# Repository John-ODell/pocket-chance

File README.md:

Pocket Chance (J'Boy) - John O'Dell

A pocket casino for the Waveshare RP2040-Plus and the Waveshare 1.3" LCD HAT, written in MicroPython. It runs offline on the board. Three games: Blackjack, Ultimate Texas Hold'em and John's own Caribbean, a flop game with a low or high call.

The HAT plugs onto the board, so there is no wiring in this project. The pin map and everything we measured on a real board is in [`docs/HARDWARE.md`](docs/HARDWARE.md).

This project was built with a small team of AI sessions (a PM, a developer and a hardware expert) directing one person. How that works, with role files and starter prompts you can reuse, is in [`docs/AI_TEAM.md`](docs/AI_TEAM.md).

Last updated: 2026-10-04

## Items needed
- Waveshare RP2040-Plus (16 MB version)
- Waveshare Pico LCD 1.3" HAT (240 x 240 screen, joystick, 4 buttons)
- USB-C data cable
- A computer with Python 3.9 or newer

## Quick start
The full follow-along guide is [`SETUP.md`](SETUP.md). The short version:

1. Download the **16 MB** MicroPython firmware for the RP2040-Plus from micropython.org. Hold BOOTSEL, plug in, drag the `.uf2` onto the `RPI-RP2` drive.
2. `pip install mpremote pillow`
3. Copy the files to the board with `mpremote fs cp` (exact commands in `SETUP.md`, Step 4).
4. `mpremote run pocket.py`

You should see the menu: "Pocket Chance", your chips, and the games.

If the screen stays dark, open `pocket.py` and set `FAST_SPI = False`. That is the only board-specific setting (see `docs/HARDWARE.md`, "The one trap").

## Controls
Landscape, with USB-C and the joystick on the left and the buttons on the right.

| Where | Control | Does |
|---|---|---|
| Menu | Joystick up / down | Move the box (the list scrolls) |
| Menu | **A** | Pick a game. "Off" stops the program |
| Blackjack, betting | Joystick up / down | Change the bet (5 to 500, steps of 5) |
| Blackjack, betting | **A** deal, **B** back to menu | |
| Blackjack, playing | **A** hit, **B** stand, **X** double, **Y** split a pair | |
| Ultimate, betting | Joystick, **A** deal, **X** help, **B** menu | Blind equals the Ante |
| Ultimate, pre-flop / flop / river | **A** raise (4x / 2x / 1x), **Y** raise 3x pre-flop, **B** check (fold at the river) | The table cards turn as you go; the river prompt shows the dealer outs |
| Caribbean, betting | Joystick up / down, left / right | Change the Ante (5 to 50, capped at a fifth of your chips) |
| Caribbean, betting | **A** deal, **X** help, **B** menu | |
| Caribbean, flop | **A** call high (4x the Ante), **Y** call low (2x), **B** fold | The last two table cards turn, then the dealer's cards one by one |

## Games

| Game | Status | Rules | House edge |
|---|---|---|---|
| Blackjack | **Playable** | 6 decks, reshuffle at 75% dealt, dealer stands on all 17, blackjack pays 3:2, hit / stand / double, split pairs once (aces get one card each, double after split allowed) | about 0.55% |
| Ultimate Texas Hold'em ("Ultimate") | **Playable** | Equal Ante and Blind (5 to 50), two hole cards, five table cards; raise 4x or 3x pre-flop, 2x after the flop, 1x at the river or fold; dealer needs a pair for the Ante to count; Blind pays straight 1:1 up to royal 500:1. X teaches the full published simple strategy and the river prompt shows the dealer-outs count (`UTH_HINT`). Four other players sit at the sides as chip stacks (`UTH_SEATS`) | about 2.4% of the ante with the taught strategy, 2.2% optimal |
| Caribbean (John's flop game) | **Playable** | Ante 5 to 50, two cards each, the first three table cards turn, then call high (4x) or low (2x) or fold, the last two turn; best five of seven; the dealer needs a pair of fours or better, otherwise every bet pushes; a winning Ante pays by a table (flush 2:1, full house 3:1, quads 10:1, straight flush 20:1, royal 100:1, else 1:1), the call 1:1. When you and all four seats beat a dealer hand, a win on the next hand pays three times (Ante and call together). Four chip-stack seats (`CAR_SEATS`). The published game this is based on is Casino Hold'em (one call size, 2.16% optimal) | about 5% of the ante with the taught strategy (15% without the multiplier) |
| Caribbean Stud | Archived (John's ruling, 2026-10-06) | Was on the board as "Caribbean" until step 1n; code in `archive/stud/` | 5.2% |
| Slots | Shelved | A 3-reel machine was built and tuned (93.84% return) then dropped: a classic multi-line machine does not fit the board's RAM. Code kept in `archive/slots/` | n/a |

Chips: you start with 1000. If you go broke you get a free refill. Your chips are saved to the board after every round, with a backup copy and recovery if the save is damaged.

The house edges were measured by simulation (`tools/bj_edge.py`, `tools/bj_split.py`, `tools/uth_edge.py`, `tools/casino_holdem_edge.py`; `archive/stud/stud_edge.py` for the archived game) and the rules were checked against the public references on wizardofodds.com.

## What it does well on this hardware
- Full-speed screen: about 58 frames a second for a full redraw, once the board's peripheral clock is set from the system PLL (one `machine.freq` call at the top of `pocket.py`, see `docs/HARDWARE.md`).
- Redraws only the strip of the screen that changed, so a button press answers in about 15 to 100 ms.
- About 50 to 55 KB of RAM left while playing, on a board with 264 KB.
- Art is optional. With no image files the game draws cards and the table in code.

## Your own art (optional)
Sizes, names, and where text sits on each screen are in [`assets/ASSETS.md`](assets/ASSETS.md). In short: draw one 24-bit BMP per picture, magenta (255, 0, 255) is transparent, run `python3 tools/convert_assets.py`, and copy the files it writes to `/assets/` on the board. The menu background is a full-screen 240 x 240 image you supply yourself (`assets/src/ui/menu_background.bmp`). None is included.

## Repository layout
```
pocket.py          the game's start file on the board (menu)
lib/               shared modules for the board: screen, fonts, buttons, images, saving, cards, clock fix, poker
games/             one set of modules per game: rules, table logic, screens
archive/           shelved work (slots)
assets/            art spec and the converter's input and output folders
tools/             Mac-side tools: image converter, odds simulators, upload checker
tests/             automated tests (run on a computer, no board needed)
hw/ hwtest/        measured hardware budget, board notes, reviews, and the benchmark scripts
docs/              hardware reference sheet, the AI team guide, role files
pcb/               workspace for designing your own board from this hardware (first-timer guide, in progress)
pm/                decision requests, rulings, decision log, hand-off notes
SETUP.md           follow-along install guide
UPLOAD.md          exact file list for the board, checked by tools/check_upload.py
main_monolith.py   the original single-file program this project replaced (read-only)
```

## Running the tests
```bash
python3 -m unittest discover -s tests
```
They run on a normal computer with stand-in modules for the board.

## Troubleshooting
| What you see | What to do |
|---|---|
| The board does not show up | Use a data cable. Close Viper IDE and its tab: only one program can use the USB port at a time |
| Dark screen | `FAST_SPI = False` in `pocket.py` |
| "no module named ..." | A file is missing or in the wrong folder. Compare with `SETUP.md`, Step 4 |
| "could not enter raw repl" | The board is fine. Unplug it, or run `hwtest/unwedge.py` |

More in [`SETUP.md`](SETUP.md).

## Credits
- The screen driver and font in `main_monolith.py`, and the code adapted from it, started from Tony Goodhew's Waveshare 1.3" workout (August 2021).
- Rules and house edges were checked against the public pages on wizardofodds.com.
- MicroPython firmware is a public download from micropython.org and is not stored here.
- Waveshare datasheets and demo code are not included.

## Issues
Open an issue with the step you were on, what you saw, and the full terminal output. Please do not post anything private.

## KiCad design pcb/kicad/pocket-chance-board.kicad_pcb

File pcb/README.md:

# pcb/: designing your own board

This folder is the workspace for turning the Pocket Chance hardware (a Waveshare RP2040-Plus plus a 1.3" LCD HAT) into **your own dev board**, ordered from a PCB fab such as PCBWay or JLCPCB. It is for someone doing this the first time.

**Status:** workspace set up. **Stage 1 (understand, no design choices)** comes first: the PCB maker writes `CONSTRAINTS.md` and `HOW_A_BOARD_IS_MADE.md`. Stage 2, what the first design adds, starts when the owner says so. See [`PLAN.md`](PLAN.md).

| File | What it is |
|---|---|
| [`PLAN.md`](PLAN.md) | The roadmap, the decisions to make first, rough costs, risks, and tools |
| [`INTAKE.md`](INTAKE.md) | What to read before designing: the project's measured hardware notes and the manufacturer documents |
| [`requirements/REQUIREMENTS.md`](requirements/REQUIREMENTS.md) | What the new board must do, with the source of every fact |
| [`../docs/roles/PCB_MAKER.md`](../docs/roles/PCB_MAKER.md) | The role file and starter prompt for the Claude session that guides you |
| `kicad/`, `bom/`, `fab/`, `reviews/` | KiCad project, bill of materials, files for the fab, and design reviews (empty for now) |
| `refs/` | Local copies of datasheets. **Not committed** (git ignores it) |

## How to start
1. Open a new Claude Code session in the repo folder and paste the starter prompt from `docs/roles/PCB_MAKER.md`.
2. Install KiCad (free): `brew install --cask kicad`, or download it from kicad.org.
3. Put the manufacturer PDFs you own into `pcb/refs/`.
4. Answer the questions one at a time. The PCB maker teaches each step.

## Request and review numbering (PM ruling, 2026-10-04)
PCB decision requests use their own prefix so they never clash with the developer's: `pm/inbox/PCB-001-slug.md`, rulings `pm/outbox/PCB-001.md`, and the expert's reviews of them `hw/reviews/HR-P01.md`. The one exception is the first scope request, which keeps its original number: `pm/inbox/DR-033-board-scope.md` (reviewed in `hw/reviews/HR-033.md`).

The PCB maker prepares everything for ordering and gives you a checklist. **You** place the order and enter payment details. It never does.

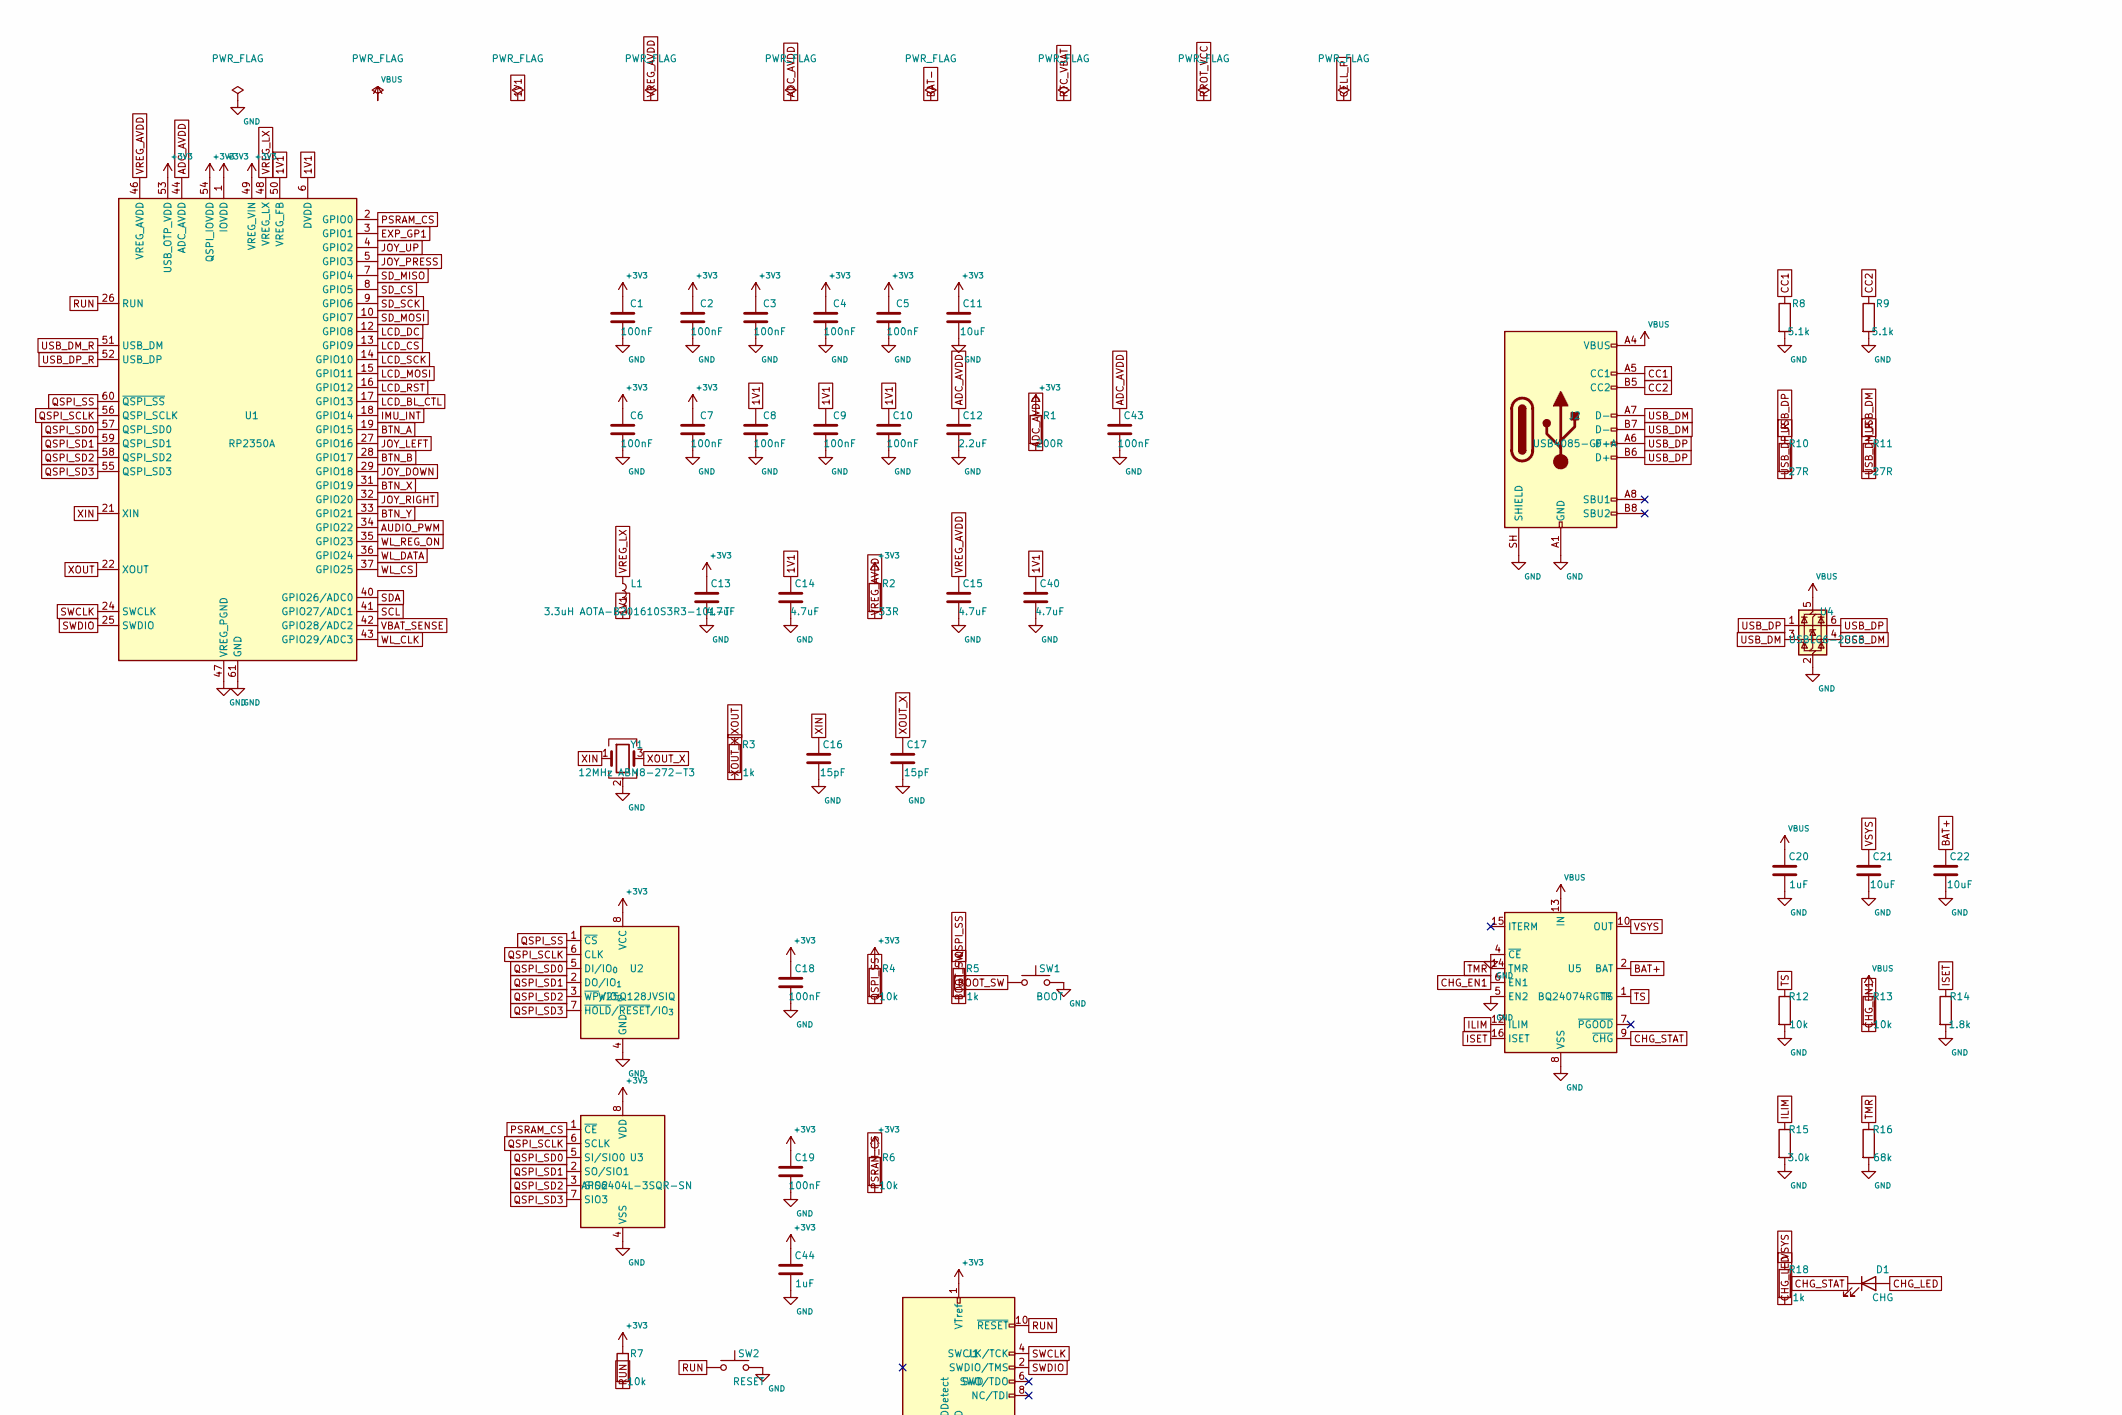
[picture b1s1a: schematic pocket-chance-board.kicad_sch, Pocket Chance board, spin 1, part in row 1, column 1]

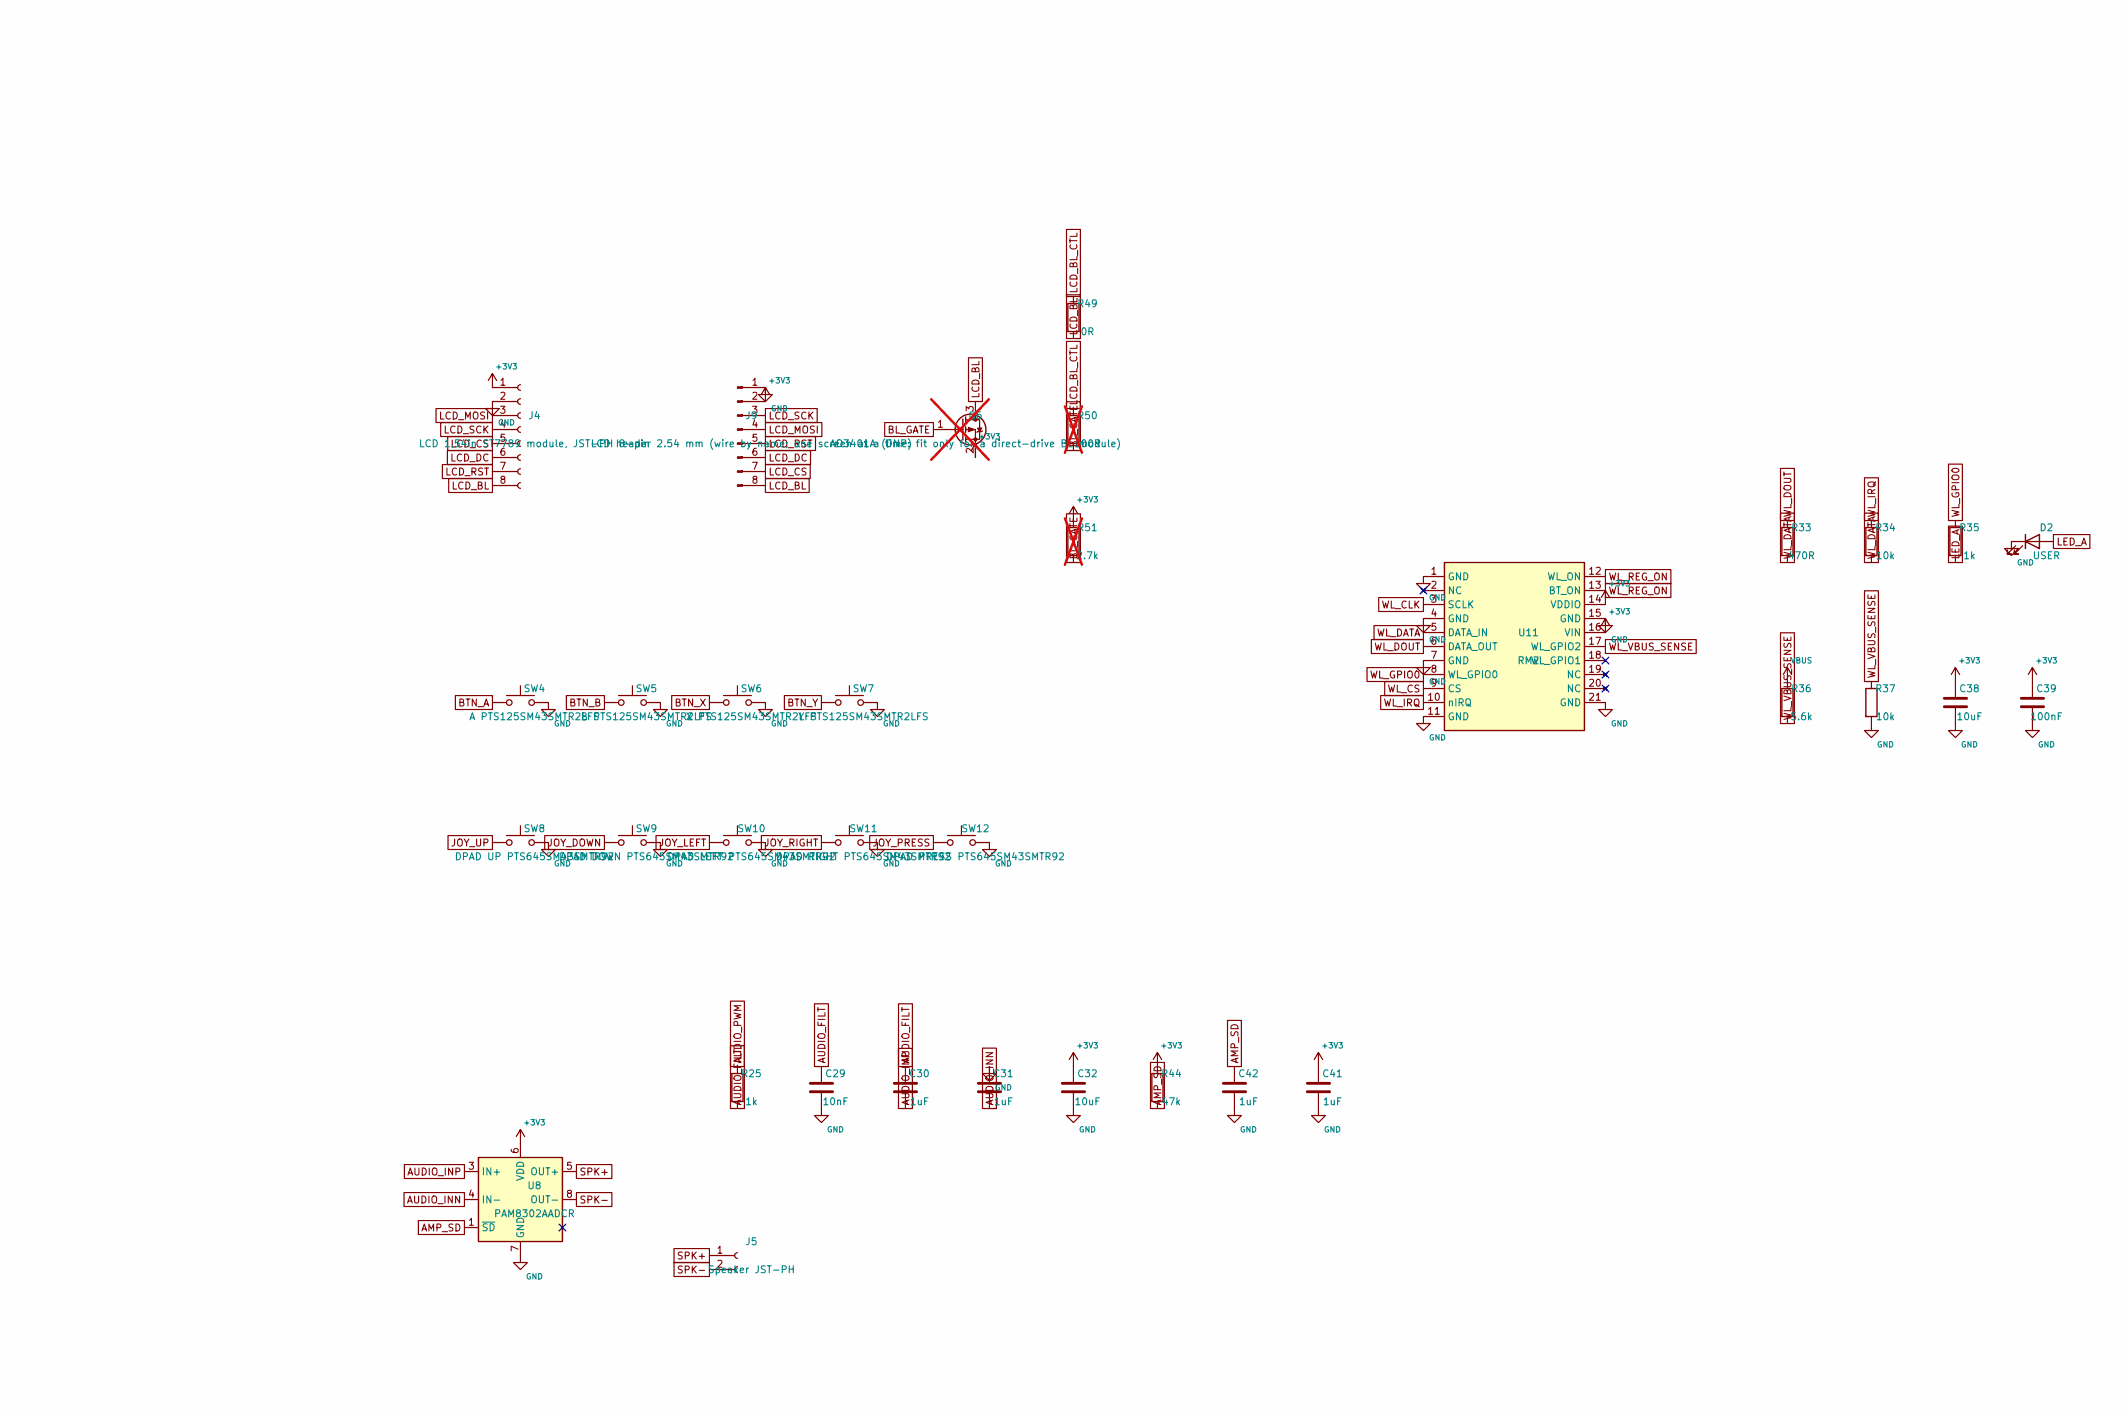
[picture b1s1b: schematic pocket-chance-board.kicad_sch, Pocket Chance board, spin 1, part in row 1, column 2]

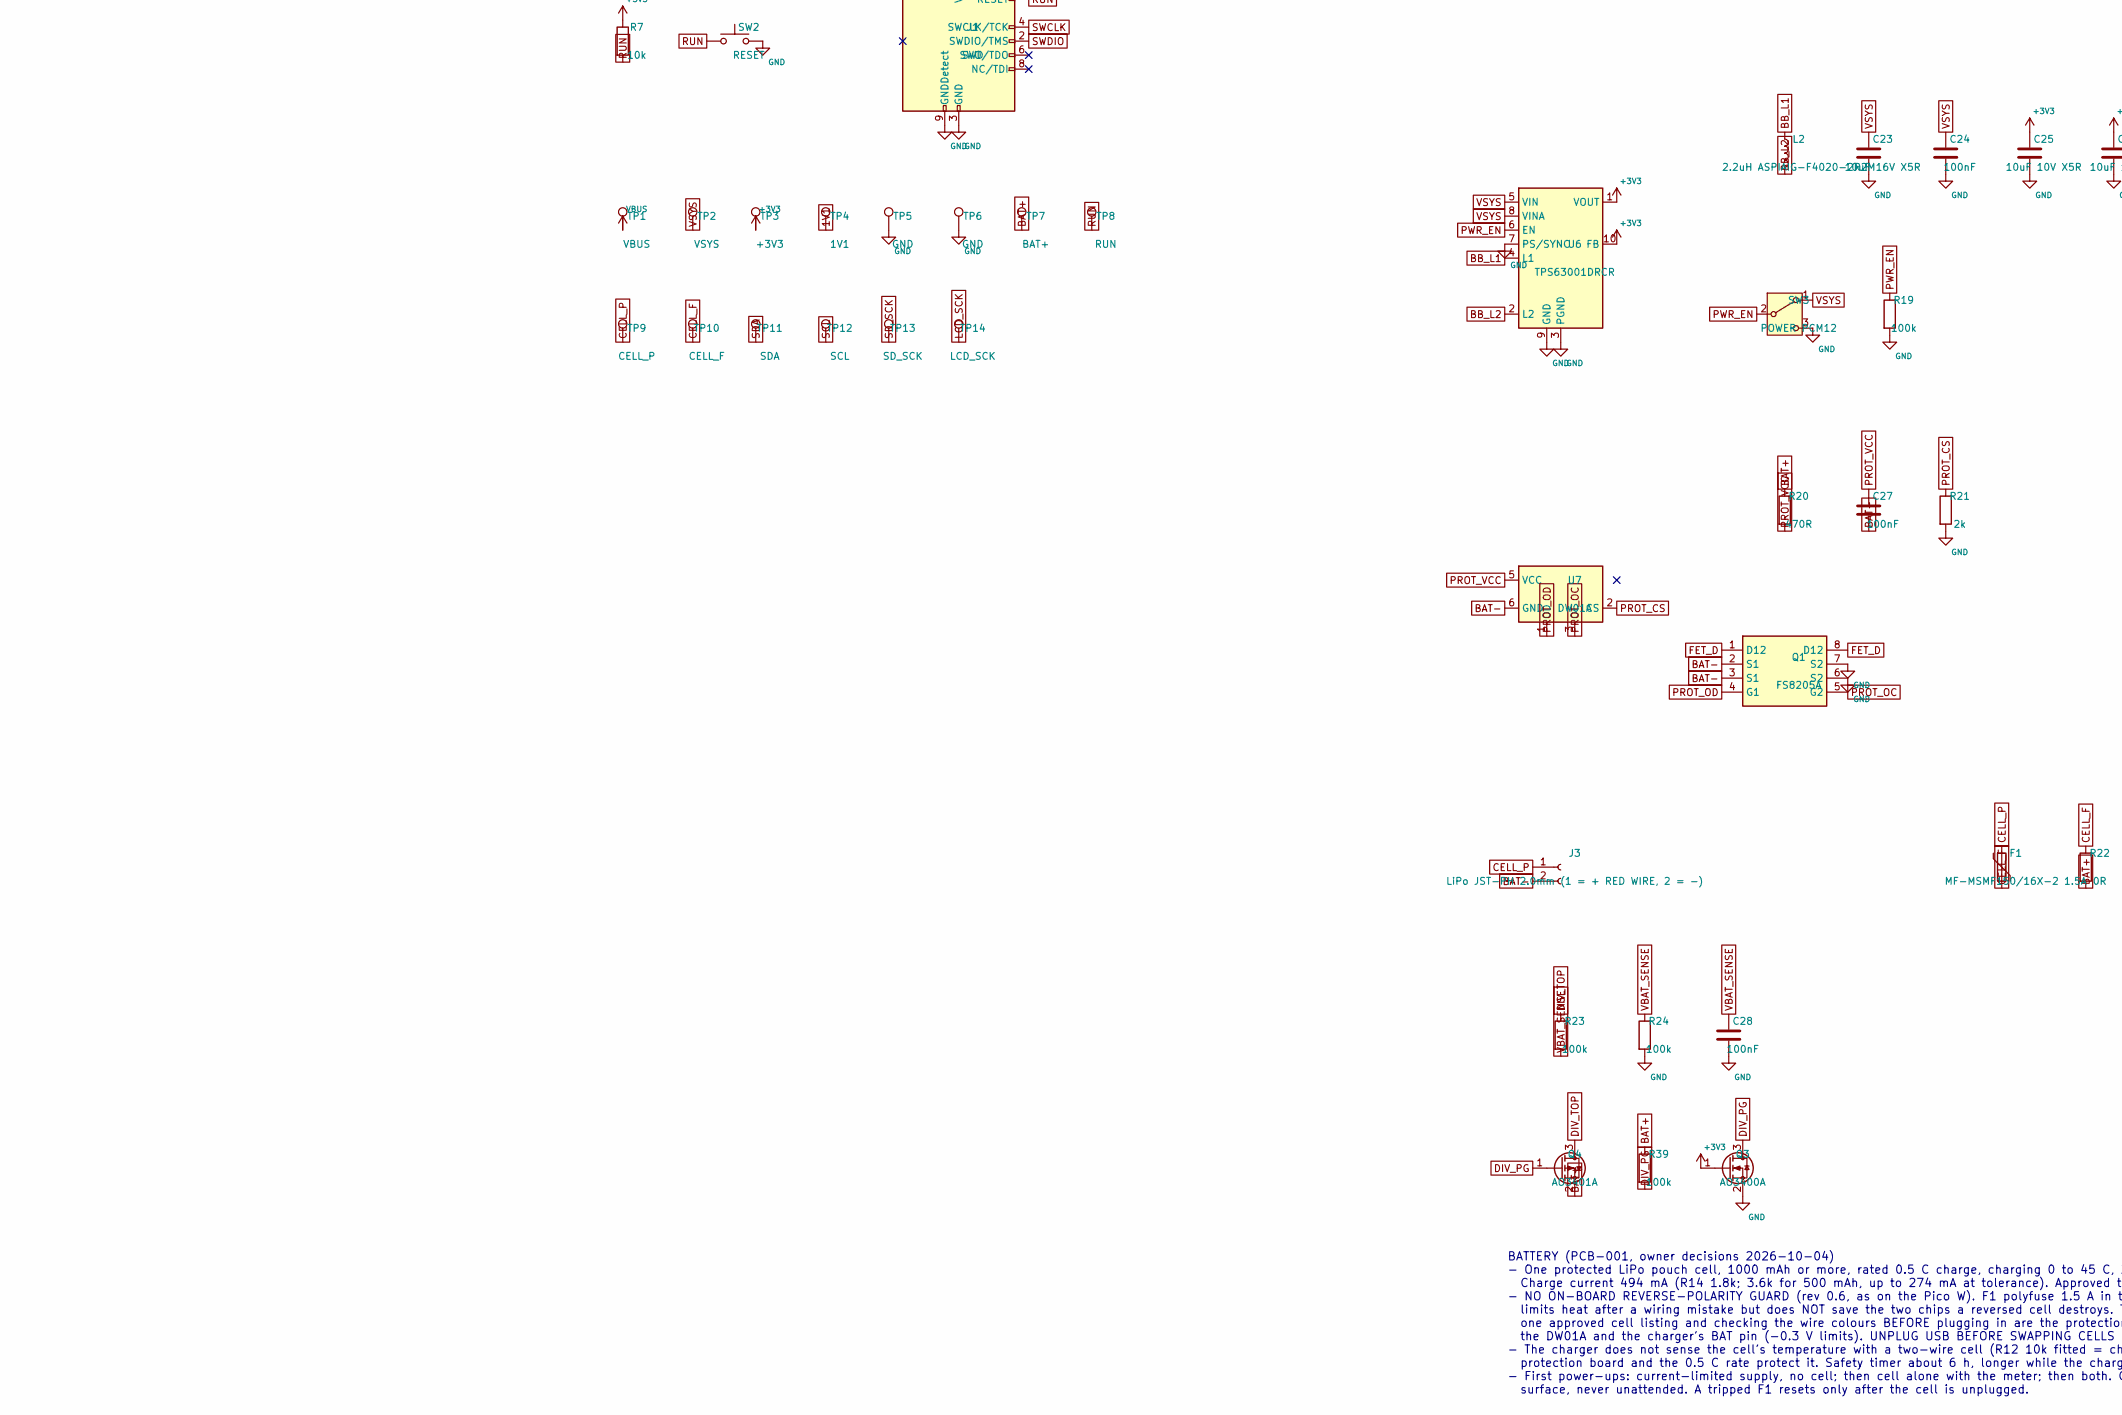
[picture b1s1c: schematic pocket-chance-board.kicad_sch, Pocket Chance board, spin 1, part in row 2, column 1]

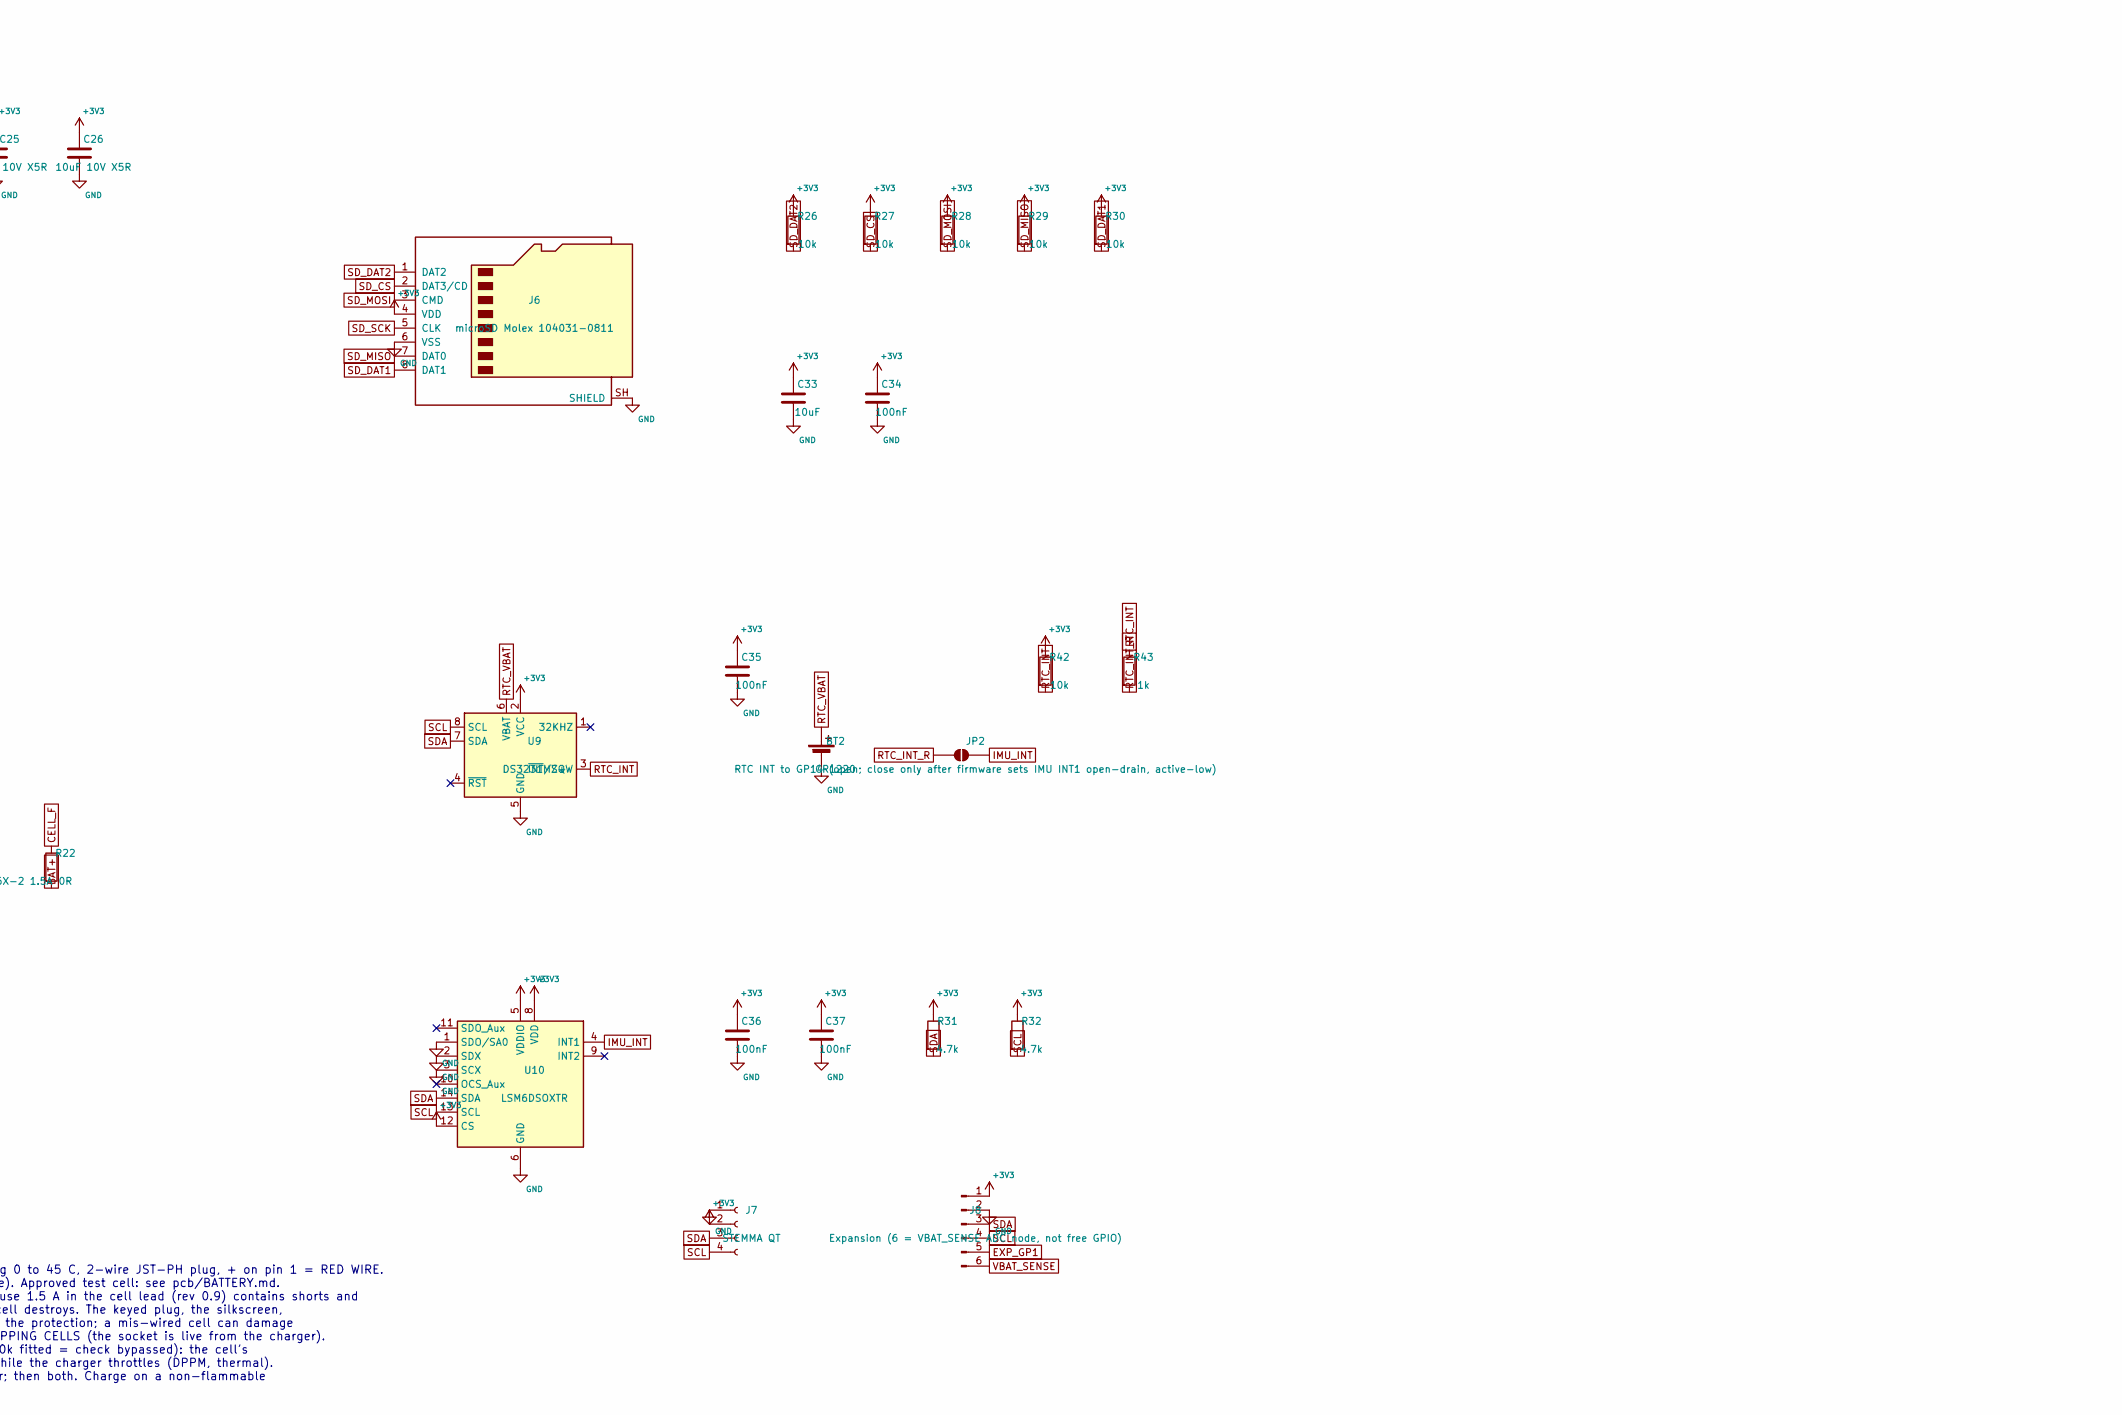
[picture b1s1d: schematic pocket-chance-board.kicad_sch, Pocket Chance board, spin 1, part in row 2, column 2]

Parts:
BT2: CR1220; BatteryHolder_Keystone_3001_1x12mm
C1, C2, C3, C4, C5, C6, C7, C8, C9, C10, C18, C19, C24, C27, C28, C34, C35, C36, C37, C39, C43: 100nF; C_0402_1005Metric
C11, C21, C22, C32, C33, C38: 10uF; C_0603_1608Metric
C12: 2.2uF; C_0603_1608Metric
C13, C14, C15, C40: 4.7uF; C_0402_1005Metric
C16, C17: 15pF; C_0402_1005Metric
C20, C30, C31, C41, C42, C44: 1uF; C_0603_1608Metric
C23: 10uF 16V X5R; C_0805_2012Metric
C25, C26: 10uF 10V X5R; C_0805_2012Metric
C29: 10nF; C_0402_1005Metric
D1: CHG; LED_0603_1608Metric
D2: USER; LED_0603_1608Metric
F1: MF-MSMF150/16X-2 1.5A; Fuse_Bourns_MF-MSMF_1812
J1: SWD; PinHeader_2x05_P1.27mm_Vertical_SMD
J2: USB4085-GF-A; USB_C_Receptacle_GCT_USB4085
J3: LiPo JST-PH 2.0mm (1 = + RED WIRE, 2 = -); JST_PH_S2B-PH-SM4-TB_1x02-1MP_P2.00mm_Horizontal
J4: LCD 1.54in ST7789 module, JST-PH 8-pin; JST_PH_S8B-PH-SM4-TB_1x08-1MP_P2.00mm_Horizontal
J5: Speaker JST-PH; JST_PH_S2B-PH-SM4-TB_1x02-1MP_P2.00mm_Horizontal
J6: microSD Molex 104031-0811; microSD_HC_Molex_104031-0811
J7: STEMMA QT; JST_SH_SM04B-SRSS-TB_1x04-1MP_P1.00mm_Horizontal
J8: Expansion (6 = VBAT_SENSE ADC node, not free GPIO); PinHeader_1x06_P2.54mm_Vertical
J9: LCD header 2.54 mm (wire by name; one screen at a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; PinHeader_1x08_P2.54mm_Vertical
JP2: RTC INT to GP14 (open; close only after firmware 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; SolderJumper-2_P1.3mm_Open_Pad1.0x1.5mm
L1: 3.3uH AOTA-B201610S3R3-101-T; AOTA-B201610S
L2: 2.2uH ASPIAIG-F4020-2R2M; L_Abracon_ASPIAIG-F4020
Q1: FS8205A; TSSOP-8_4.4x3mm_P0.65mm
Q3: AO3400A; SOT-23
Q4: AO3401A; SOT-23
Q6: AO3401A (DNP: fit only for a direct-drive BL modu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; SOT-23; not fitted
R1: 200R; R_0402_1005Metric
R2: 33R; R_0402_1005Metric
R3, R5, R18, R25, R35, R43: 1k; R_0402_1005Metric
R4, R6, R7, R12, R13, R26, R27, R28, R29, R30, R34, R37, R42: 10k; R_0402_1005Metric
R8, R9: 5.1k; R_0402_1005Metric
R10, R11: 27R; R_0402_1005Metric
R14: 1.8k; R_0402_1005Metric
R15: 3.0k; R_0402_1005Metric
R16: 68k; R_0402_1005Metric
R19, R23, R24, R39: 100k; R_0402_1005Metric
R20, R33: 470R; R_0402_1005Metric
R21: 2k; R_0402_1005Metric
R22: 0R; R_0603_1608Metric
R31, R32: 4.7k; R_0402_1005Metric
R36: 5.6k; R_0402_1005Metric
R44: 47k; R_0402_1005Metric
R49: 0R; R_0402_1005Metric
R50: 100R; R_0402_1005Metric; not fitted
R51: 2.7k; R_0402_1005Metric; not fitted
SW1: BOOT; SW_SPST_PTS645Sx43SMTR92
SW2: RESET; SW_SPST_PTS645Sx43SMTR92
SW3: POWER PCM12; SW_SPDT_PCM12
SW4: A PTS125SM43SMTR2LFS; SW_Push_1P1T_NO_CK_PTS125Sx43SMTR
SW5: B PTS125SM43SMTR2LFS; SW_Push_1P1T_NO_CK_PTS125Sx43SMTR
SW6: X PTS125SM43SMTR2LFS; SW_Push_1P1T_NO_CK_PTS125Sx43SMTR
SW7: Y PTS125SM43SMTR2LFS; SW_Push_1P1T_NO_CK_PTS125Sx43SMTR
SW8: DPAD UP PTS645SM43SMTR92; SW_SPST_PTS645Sx43SMTR92
SW9: DPAD DOWN PTS645SM43SMTR92; SW_SPST_PTS645Sx43SMTR92
SW10: DPAD LEFT PTS645SM43SMTR92; SW_SPST_PTS645Sx43SMTR92
SW11: DPAD RIGHT PTS645SM43SMTR92; SW_SPST_PTS645Sx43SMTR92
SW12: DPAD PRESS PTS645SM43SMTR92; SW_SPST_PTS645Sx43SMTR92
TP1: VBUS; TestPoint_Pad_D1.5mm
TP2: VSYS; TestPoint_Pad_D1.5mm
TP3: +3V3; TestPoint_Pad_D1.5mm
TP4: 1V1; TestPoint_Pad_D1.5mm
TP5, TP6: GND; TestPoint_Pad_D1.5mm
TP7: BAT+; TestPoint_Pad_D1.5mm
TP8: RUN; TestPoint_Pad_D1.5mm
TP9: CELL_P; TestPoint_Pad_D1.5mm
TP10: CELL_F; TestPoint_Pad_D1.5mm
TP11: SDA; TestPoint_Pad_D1.5mm
TP12: SCL; TestPoint_Pad_D1.5mm
TP13: SD_SCK; TestPoint_Pad_D1.5mm
TP14: LCD_SCK; TestPoint_Pad_D1.5mm
U1: RP2350A; QFN-60-1EP_7x7mm_P0.4mm_EP3.4x3.4mm
U2: W25Q128JVSIQ; SOIC-8_5.3x5.3mm_P1.27mm
U3: APS6404L-3SQR-SN; SOIC-8_3.9x4.9mm_P1.27mm
U4: USBLC6-2SC6; SOT-23-6
U5: BQ24074RGTR; VQFN-16-1EP_3x3mm_P0.5mm_EP1.68x1.68mm_ThermalVias
U6: TPS63001DRCR; Texas_DRC0010J_ThermalVias
U7: DW01A; SOT-23-6
U8: PAM8302AADCR; SOIC-8_3.9x4.9mm_P1.27mm
U9: DS3231MZ+; SOIC-8_3.9x4.9mm_P1.27mm
U10: LSM6DSOXTR; LGA-14_3x2.5mm_P0.5mm_LayoutBorder3x4y
U11: RM2
Y1: 12MHz ABM8-272-T3; Crystal_SMD_3225-4Pin_3.2x2.5mm

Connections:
1V1: C8.1, C9.1, C10.1, C14.1, C40.1, L1.2, TP4.1, U1.6 (DVDD), U1.23 (DVDD), U1.39 (DVDD), U1.50 (VREG_FB)
+3V3: C1.1, C2.1, C3.1, C4.1, C5.1, C6.1, C7.1, C11.1, C13.1, C18.1, C19.1, C25.1, C26.1, C32.1, C33.1, C34.1, C35.1, C36.1, C37.1, C38.1, C39.1, C41.1, C44.1, J1.1 (VTref), J4.1, J6.4 (VDD), J7.2, J8.1, J9.2, Q3.1 (G), Q6.2 (S), R1.1, R2.1, R4.1, R6.1, R7.1, R26.1, R27.1, R28.1, R29.1, R30.1, R31.1, R32.1, R42.1, R44.1, R51.1, TP3.1, U1.1 (IOVDD), U1.11 (IOVDD), U1.20 (IOVDD), U1.30 (IOVDD), U1.38 (IOVDD), U1.45 (IOVDD), U1.49 (VREG_VIN), U1.53 (USB_OTP_VDD), U1.54 (QSPI_IOVDD), U2.8 (VCC), U3.8 (VDD), U6.1 (VOUT), U6.10 (FB), U8.6 (VDD), U9.2 (VCC), U10.5 (VDDIO), U10.8 (VDD), U10.12 (CS), U11.14 (VDDIO), U11.16 (VIN)
ADC_AVDD: C12.1, C43.1, R1.2, U1.44 (ADC_AVDD)
AMP_SD: C42.1, R44.2, U8.1 (~SD)
AUDIO_FILT: C29.1, C30.1, R25.2
AUDIO_INN: C31.2, U8.4 (IN-)
AUDIO_INP: C30.2, U8.3 (IN+)
AUDIO_PWM: R25.1, U1.34 (GPIO22)
BAT+: C22.1, Q4.2 (S), R20.1, R22.2, R39.1, TP7.1, U5.2 (BAT), U5.3 (BAT)
BAT-: C27.2, J3.2, Q1.2 (S1), Q1.3 (S1), U7.6 (GND)
BB_L1: L2.1, U6.4 (L1)
BB_L2: L2.2, U6.2 (L2)
BL_GATE: Q6.1 (G), R50.2, R51.2
BOOT_SW: R5.2, SW1.1
BTN_A: SW4.1, U1.19 (GPIO15)
BTN_B: SW5.1, U1.28 (GPIO17)
BTN_X: SW6.1, U1.31 (GPIO19)
BTN_Y: SW7.1, U1.33 (GPIO21)
CC1: J2.A5 (CC1), R8.1
CC2: J2.B5 (CC2), R9.1
CELL_F: F1.2, R22.1, TP10.1
CELL_P: F1.1, J3.1, TP9.1
CHG_EN1: R13.2, U5.6 (EN1)
CHG_LED: D1.2 (A), R18.2
CHG_STAT: D1.1 (K), U5.9 (~CHG)
DIV_PG: Q3.3 (D), Q4.1 (G), R39.2
DIV_TOP: Q4.3 (D), R23.1
EXP_GP1: J8.5, U1.3 (GPIO1)
FET_D: Q1.1 (D12), Q1.8 (D12)
GND: BT2.2 (-), C1.2, C2.2, C3.2, C4.2, C5.2, C6.2, C7.2, C8.2, C9.2, C10.2, C11.2, C12.2, C13.2, C14.2, C15.2, C16.2, C17.2, C18.2, C19.2, C20.2, C21.2, C22.2, C23.2, C24.2, C25.2, C26.2, C28.2, C29.2, C31.1, C32.2, C33.2, C34.2, C35.2, C36.2, C37.2, C38.2, C39.2, C40.2, C41.2, C42.2, C43.2, C44.2, D2.1 (K), J1.3 (GND), J1.5 (GND), J1.9 (GNDDetect), J2.A1 (GND), J2.A12 (GND), J2.B1 (GND), J2.B12 (GND), J2.SH (SHIELD), J4.2, J6.6 (VSS), J6.SH (SHIELD), J7.1, J8.2, J9.1, Q1.6 (S2), Q1.7 (S2), Q3.2 (S), R8.2, R9.2, R12.2, R14.2, R15.2, R16.2, R19.2, R21.2, R24.2, R37.2, SW1.2, SW2.2, SW3.3 (C), SW4.2, SW5.2, SW6.2, SW7.2, SW8.2, SW9.2, SW10.2, SW11.2, SW12.2, TP5.1, TP6.1, U1.47 (VREG_PGND), U1.61 (GND), U2.4 (GND), U3.4 (VSS), U4.2 (GND), U5.4 (~CE), U5.5 (EN2), U5.8 (VSS), U5.17 (VSS), U6.3 (PGND), U6.7 (PS/SYNC), U6.9 (GND), U6.11 (PGND), U8.7 (GND), U9.5 (GND), U10.1 (SDO/SA0), U10.2 (SDX), U10.3 (SCX), U10.6 (GND), U10.7 (GND), U11.1 (GND), U11.4 (GND), U11.7 (GND), U11.11 (GND), U11.15 (GND), U11.21 (GND), Y1.2 (G), Y1.4 (G)
ILIM: R15.1, U5.12 (ILIM)
IMU_INT: JP2.2 (B), U1.18 (GPIO14), U10.4 (INT1)
ISET: R14.1, U5.16 (ISET)
JOY_DOWN: SW9.1, U1.29 (GPIO18)
JOY_LEFT: SW10.1, U1.27 (GPIO16)
JOY_PRESS: SW12.1, U1.5 (GPIO3)
JOY_RIGHT: SW11.1, U1.32 (GPIO20)
JOY_UP: SW8.1, U1.4 (GPIO2)
LCD_BL: J4.8, J9.8, Q6.3 (D), R49.2
LCD_BL_CTL: R49.1, R50.1, U1.17 (GPIO13)
LCD_CS: J4.5, J9.7, U1.13 (GPIO9)
LCD_DC: J4.6, J9.6, U1.12 (GPIO8)
LCD_MOSI: J4.3, J9.4, U1.15 (GPIO11)
LCD_RST: J4.7, J9.5, U1.16 (GPIO12)
LCD_SCK: J4.4, J9.3, TP14.1, U1.14 (GPIO10)
LED_A: D2.2 (A), R35.2
PROT_CS: R21.1, U7.2 (CS)
PROT_OC: Q1.5 (G2), U7.3 (OC)
PROT_OD: Q1.4 (G1), U7.1 (OD)
PROT_VCC: C27.1, R20.2, U7.5 (VCC)
PSRAM_CS: R6.2, U1.2 (GPIO0), U3.1 (~CE)
PWR_EN: R19.1, SW3.2 (B), U6.6 (EN)
QSPI_SCLK: U1.56 (QSPI_SCLK), U2.6 (CLK), U3.6 (SCLK)
QSPI_SD0: U1.57 (QSPI_SD0), U2.5 (DI/IO_{0}), U3.5 (SI/SIO0)
QSPI_SD1: U1.59 (QSPI_SD1), U2.2 (DO/IO_{1}), U3.2 (SO/SIO1)
QSPI_SD2: U1.58 (QSPI_SD2), U2.3 (~WP/IO_{2}), U3.3 (SIO2)
QSPI_SD3: U1.55 (QSPI_SD3), U2.7 (~HOLD/~RESET/IO_{3}), U3.7 (SIO3)
QSPI_SS: R4.2, R5.1, U1.60 (~QSPI_SS), U2.1 (~CS)
RTC_INT: R42.2, R43.1, U9.3 (~INT/SQW)
RTC_INT_R: JP2.1 (A), R43.2
RTC_VBAT: BT2.1 (+), U9.6 (VBAT)
RUN: J1.10 (~RESET), R7.2, SW2.1, TP8.1, U1.26 (RUN)
SCL: J7.4, J8.4, R32.2, TP12.1, U1.41 (GPIO27/ADC1), U9.8 (SCL), U10.13 (SCL)
SDA: J7.3, J8.3, R31.2, TP11.1, U1.40 (GPIO26/ADC0), U9.7 (SDA), U10.14 (SDA)
SD_CS: J6.2 (DAT3/CD), R27.2, U1.8 (GPIO5)
SD_DAT1: J6.8 (DAT1), R30.2
SD_DAT2: J6.1 (DAT2), R26.2
SD_MISO: J6.7 (DAT0), R29.2, U1.7 (GPIO4)
SD_MOSI: J6.3 (CMD), R28.2, U1.10 (GPIO7)
SD_SCK: J6.5 (CLK), TP13.1, U1.9 (GPIO6)
SPK+: J5.1, U8.5 (OUT+)
SPK-: J5.2, U8.8 (OUT-)
SWCLK: J1.4 (SWCLK/TCK), U1.24 (SWCLK)
SWDIO: J1.2 (SWDIO/TMS), U1.25 (SWDIO)
TMR: R16.1, U5.14 (TMR)
TS: R12.1, U5.1 (TS)
USB_DM: J2.A7 (D-), J2.B7 (D-), R11.1, U4.3 (I/O2), U4.4 (I/O2)
USB_DM_R: R11.2, U1.51 (USB_DM)
USB_DP: J2.A6 (D+), J2.B6 (D+), R10.1, U4.1 (I/O1), U4.6 (I/O1)
USB_DP_R: R10.2, U1.52 (USB_DP)
VBAT_SENSE: C28.1, J8.6, R23.2, R24.1, U1.42 (GPIO28/ADC2)
VBUS: C20.1, J2.A4 (VBUS), J2.A9 (VBUS), J2.B4 (VBUS), J2.B9 (VBUS), R13.1, R36.1, TP1.1, U4.5 (VBUS), U5.13 (IN)
VREG_AVDD: C15.1, R2.2, U1.46 (VREG_AVDD)
VREG_LX: L1.1, U1.48 (VREG_LX)
VSYS: C21.1, C23.1, C24.1, R18.1, SW3.1 (A), TP2.1, U5.10 (OUT), U5.11 (OUT), U6.5 (VIN), U6.8 (VINA)
WL_CLK: U1.43 (GPIO29/ADC3), U11.3 (SCLK)
WL_CS: U1.37 (GPIO25), U11.9 (CS)
WL_DATA: R33.2, R34.2, U1.36 (GPIO24), U11.5 (DATA_IN)
WL_DOUT: R33.1, U11.6 (DATA_OUT)
WL_GPIO0: R35.1, U11.8 (WL_GPIO0)
WL_IRQ: R34.1, U11.10 (nIRQ)
WL_REG_ON: U1.35 (GPIO23), U11.12 (WL_ON), U11.13 (BT_ON)
WL_VBUS_SENSE: R36.2, R37.1, U11.17 (WL_GPIO2)
XIN: C16.1, U1.21 (XIN), Y1.1
XOUT: R3.1, U1.22 (XOUT)
XOUT_X: C17.1, R3.2, Y1.3

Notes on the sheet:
BATTERY (PCB-001, owner decisions 2026-10-04) - One protected LiPo pouch cell, 1000 mAh or more, rated 0.5 C charge, charging 0 to 45 C, 2-wire JST-PH plug, + on pin 1 = RED WIRE. Charge current 494 mA (R14 1.8k; 3.6k for 500 mAh, up to 274 mA at tolerance). Approved test cell: see pcb/BATTERY.md. 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

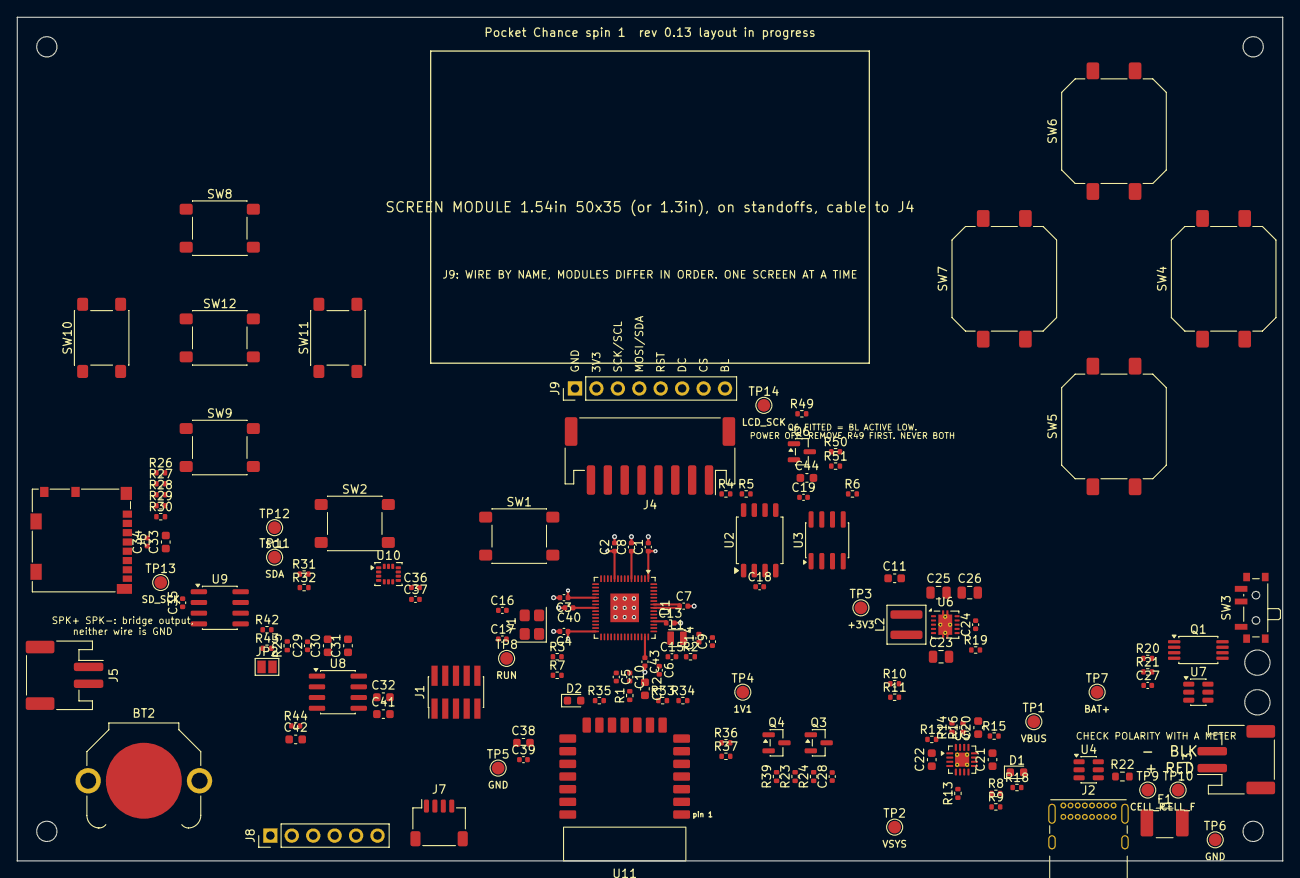
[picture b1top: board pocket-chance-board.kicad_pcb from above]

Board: 4 copper layers, 150.0 x 100.0 mm, 151 parts (0 on the bottom side), 96 nets.

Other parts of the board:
H1, H2: tie-down hole
MH1, MH2, MH3, MH4: tie-down hole
